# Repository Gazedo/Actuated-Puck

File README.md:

# Actuated-Puck

## How To Connect and Command
 1. In order to connect to the puck you must have a bluetooth serial console.
 2. After installing a serial console such as putty, connect to the puck via bluetooth.
   * It will be called BT-42
   * If asked for a passcode try either 0000 or 1234, 0000 worked for me but in reality the puck doesn't have a security passphase so either should work.
 3. From there the command set is a set of 4 digits. The first digit is a switch variable and the last 3 are the command digits. The possible combinations are:
   * s000
Sets a new degree for the Set point for the PID algorithm.
In order to set for -10 degrees, command s350.
10 degrees would be s010.
   * p000
this would set the p variable to 0, in order to set the p variable to 5, command p500 as the number will be divided by 100.
  * i000
Same as the p variable but for the integral constant.
  * d000
Same as the p variable but for the derivative constant.
  * where the 000 is any possible combination of 3 digits.
 4. There will never be any feedback from the puck as the transmit line of the UART port is used to feed information to the sd card.

## Planned upgrades
Teensy 3.1
  * Would eliminate the 5V regulator and the 3V3 regulator.
  * Enable the chip to output the logged information by bluetooth rather than having to use the sd card
  * Operates at 3V3 but is tolerant to 5V
    * Would eliminate the need for the level shifter
9 DoF IMU
  * Doesn't seem to be needed under testing however it is an option if excessive yaw drift is found which effects the readings.
##Driver Chip
  * This driver chip (L6234) needs a very specialized commutation sequence in order to make the motor move and that code has been the major obstacle but there don't seem to be any better options on the market. An ideal chip would take the hall effect signals as input, a pwm signal from the MCU as input, and output the correct drive current and voltage.

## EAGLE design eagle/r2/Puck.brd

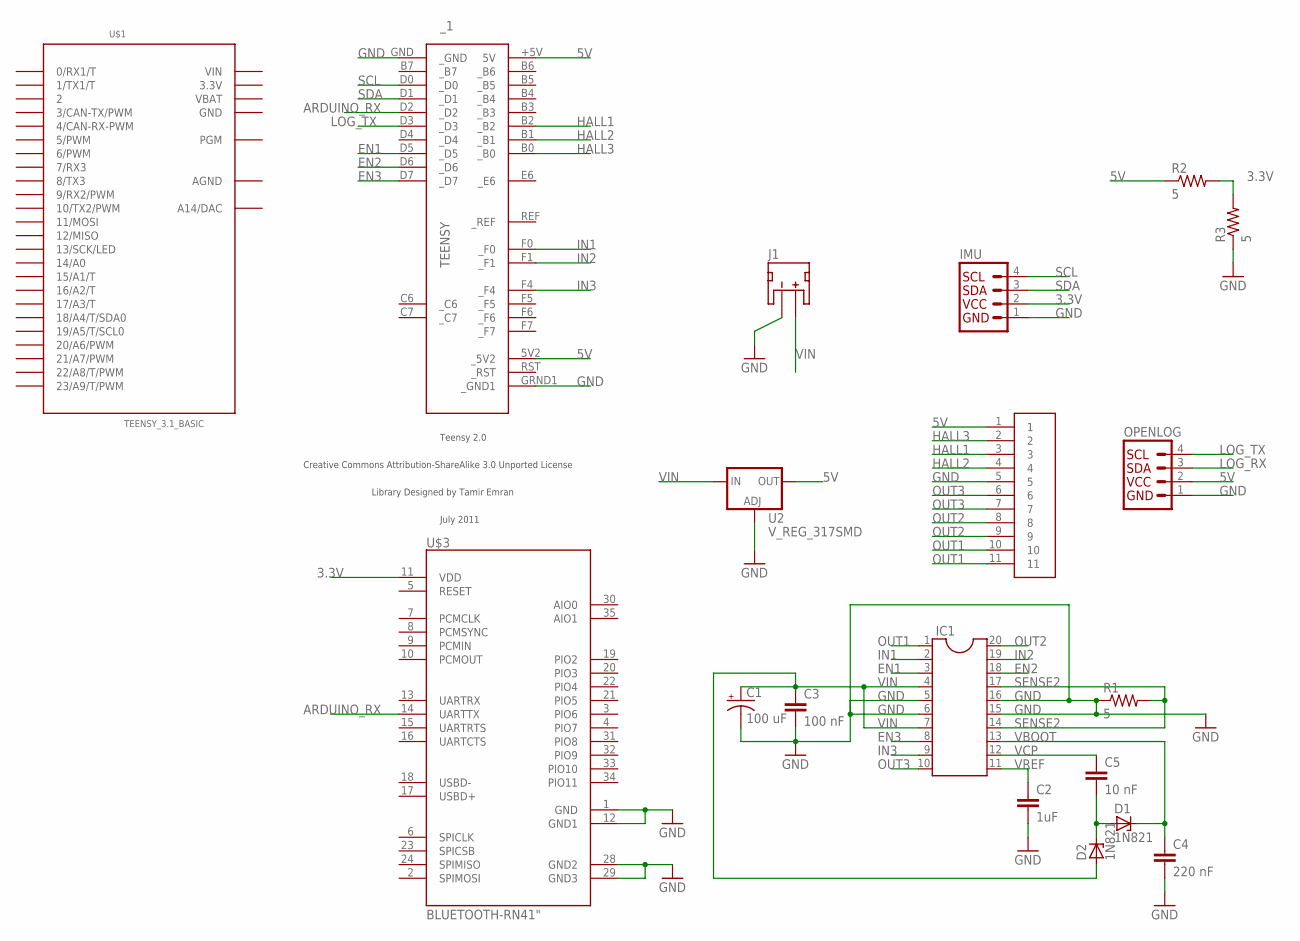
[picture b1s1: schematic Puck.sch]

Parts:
C1: 100 uF; CPOL-RADIAL-100UF-25V
C2: 1uF; CAP-PTH-SMALL-KIT
C3: 100 nF; CAP-PTH-SMALL-KIT
C4: 220 nF; CAP-PTH-SMALL-KIT
C5: 10 nF; CAP-PTH-SMALL-KIT
D1, D2: 1N821; DO35Z10
IC1: DIL20S; SOCKET-20
IMU: I2C_STANDARD; 1X04; MPN BIM-AKT-Y1X-0.4M-RS4.21T/S561
J1: JST_2MM_MALE; JST-2-SMD
MOLEX_MOTOR1: DEV; 52089FFCPACKAGE
OPENLOG: I2C_STANDARD; 1X04; MPN BIM-AKT-Y1X-0.4M-RS4.21T/S561
R1, R2, R3: 5; AXIAL-0.3
U2: V_REG_317SMD; SOT223
U$1: TEENSY_3.1_BASIC
U$3: BLUETOOTH-RN41"; RN41
_1: TEENSY

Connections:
3.3V: IMU.2, R2.P$2 (2), R3.P$2 (2), U$1.3.3V, U$1.3.3V1 (3.3V), U$3.11 (VDD)
5V: MOLEX_MOTOR1.1, OPENLOG.2, R2.P$1 (1), U2.2 (OUT), _1.5V2 (_5V2), _1.+5V (5V)
AGND: U$1.AGND
ARDUINO_RX: U$3.14 (UARTTX), _1.D2 (_D2)
EN1: IC1.3, _1.D5 (_D5)
EN2: IC1.18, _1.D6 (_D6)
EN3: IC1.8, _1.D7 (_D7)
GND: C1.2 (-), C2.2, C3.2, C4.2, IC1.5, IC1.6, IC1.15, IC1.16, IMU.1, J1.1 (-), MOLEX_MOTOR1.5, OPENLOG.1, R1.P$1 (1), R3.P$1 (1), U2.1 (ADJ), U$1.GND, U$1.GND1 (GND), U$3.1 (GND), U$3.12 (GND1), U$3.28 (GND2), U$3.29 (GND3), _1.GND (_GND), _1.GRND1 (_GND1)
HALL1: MOLEX_MOTOR1.3, _1.B2 (_B2)
HALL2: MOLEX_MOTOR1.4, _1.B1 (_B1)
HALL3: MOLEX_MOTOR1.2, _1.B0 (_B0)
IN1: IC1.2, _1.F0 (_F0)
IN2: IC1.19, _1.F1 (_F1)
IN3: IC1.9, _1.F4 (_F4)
LOG_RX: OPENLOG.3
LOG_TX: OPENLOG.4, _1.D3 (_D3)
unnamed: C5.2, D1.A, D2.C
OUT1: IC1.1, MOLEX_MOTOR1.10, MOLEX_MOTOR1.11
OUT2: IC1.20, MOLEX_MOTOR1.8, MOLEX_MOTOR1.9
OUT3: IC1.10, MOLEX_MOTOR1.6, MOLEX_MOTOR1.7
SCL: IMU.4, _1.D0 (_D0)
SDA: IMU.3, _1.D1 (_D1)
SENSE2: IC1.14, IC1.17, R1.P$2 (2)
VBAT: U$1.VBAT
VBOOT: C4.1, D1.C, IC1.13
VCP: C5.1, IC1.12
VIN: C1.1 (+), C3.1, D2.A, IC1.4, IC1.7, J1.2 (+), U2.3 (IN), U$1.VIN
VREF: C2.1, IC1.11

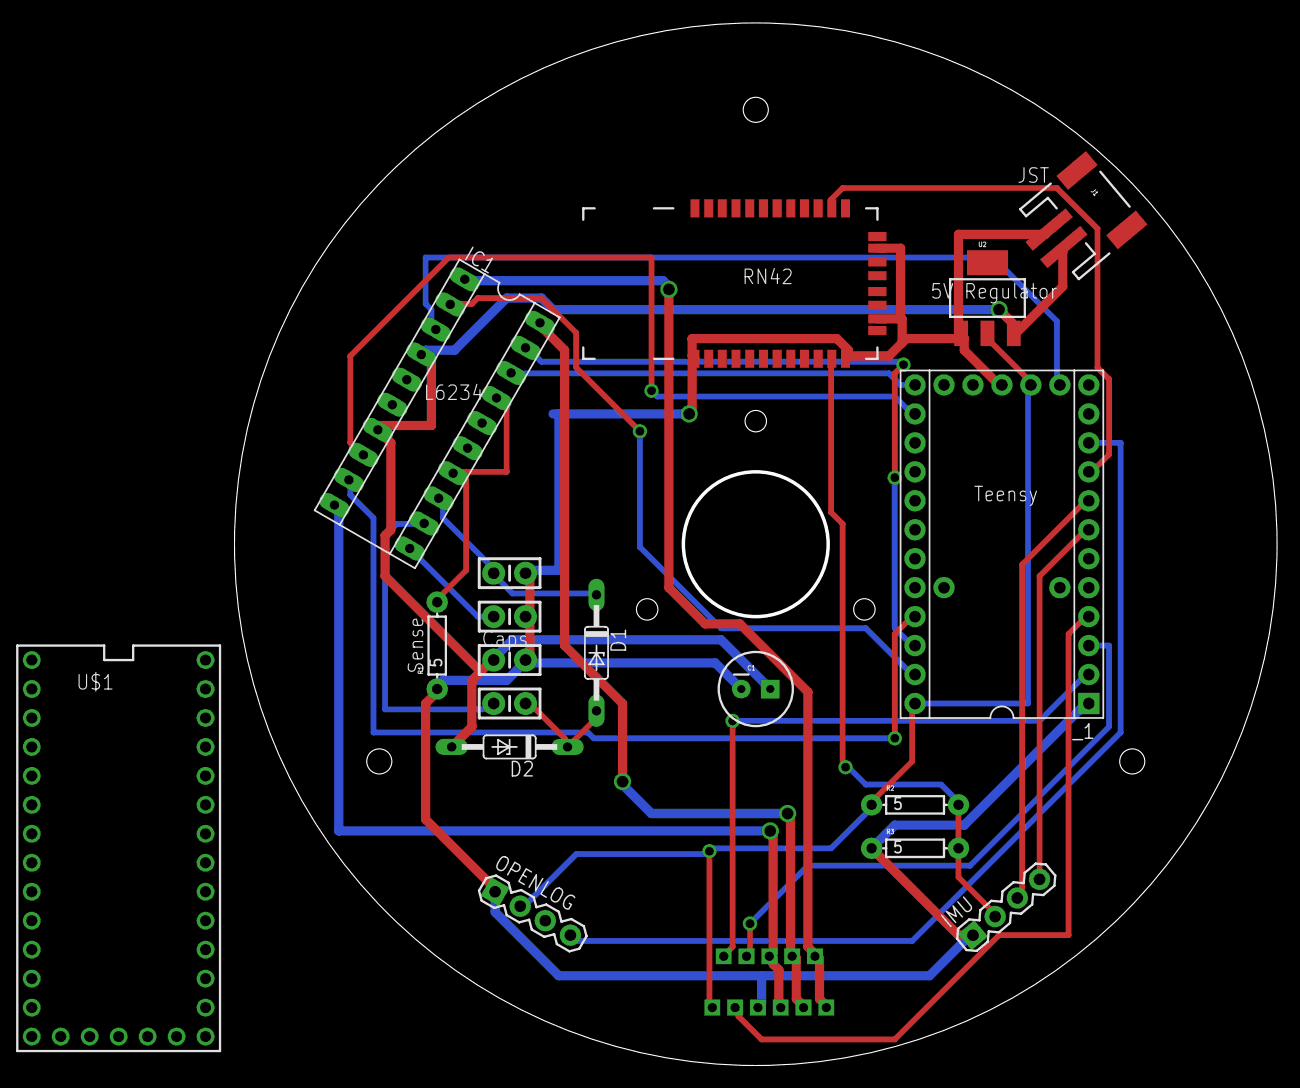
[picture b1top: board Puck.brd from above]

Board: 2 copper layers, 91.4 x 91.4 mm, 19 parts (0 on the bottom side), 25 nets.

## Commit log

2015-07-09 Initial upload of current project state
2015-07-09 Added readme for code and renamed files

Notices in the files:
parts and their libraries:
SparkFun-RF: Licensing: Creative Commons ShareAlike 4.0 International - https://creativecommons.org/licenses/by-sa/4.0
teensy: Licensed Under Creative Commons
teensy: Creative Commons Attribution-ShareAlike 3.0 Unported License
